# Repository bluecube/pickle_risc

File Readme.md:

# Pickle RISC 16bit CPU

... so I would like to build a computer, this time a little closer to "from scratch".

## Goals
- Fun!
- Aiming for a poorly defined balance between "easy to build" and "not too slow"
- Can run a multitasking OS
- Serve web site about itself (like Magic-1 does)
- Serial console interface
- Run at ~2MHz clock
    - 4MHz as a stretch goal :)
- Most instruction single cycle
- Probably RPi as a peripherial device, emulating a [GPU](notes/graphics.md), network card, storage, serial terminal...

## State
- Instruction set
    - Kind of done, still being tweaked to match the HW limitations and to improve proramming experience
- HW design
    - Slightly more than a fuzzy idea of how stuff should should go together
    - The block diagram shows most of the general idea
    - There is a [design document](design.md) that contains some (incomplete) information
- SW
    - Skeleton of a toolchain written in Rust ([toolchain-rs/](toolchain-rs/))
    - [Lisp](notes/lisp.md) interpreter is planned as a shell
        - Probably loosely based on [Make a Lisp](https://github.com/kanaka/mal/blob/master/process/guide.md)
        - Compiler as a stretch goal

## Links
### Inspiration
- Magic-1: http://www.homebrewcpu.com/
    - Showed me that there is so much magic in this topic.
    - I would like my machine to look like Magic-1 and do the stuff that Magic-1 does.
- Ben Eater's breadboard computer: https://www.youtube.com/playlist?list=PLowKtXNTBypGqImE405J2565dvjafglHU
    - Gave me the idea that I could actually build something like this.
- James Sharman's JAM-1: https://www.youtube.com/c/weirdboyjim/videos
    - Different goals, but just plain awesome :)

### Instruction set
- ARM Thumb Instruction set
- AVR instruction set

### Peripherials
- Interfacing SDHC card to 6502: https://github.com/gfoot/sdcard6502

### The rest
- MUPS/16, a nice 16bit CPU with similar goals/design: http://mups16.net/pages/overview.html#overview
- RISC-V: https://riscv.org/wp-content/uploads/2017/05/riscv-spec-v2.2.pdf
- Simple almost C-like language: https://incoherency.co.uk/blog/stories/slang.html
- Logisim evolution
- Nandgame ALU https://nandgame.com/
    > The ALU (Arithmetic/Logic Unit) performs one or more operations on two input values X and Y.
    >
    > The six flags select what operations to perform. Each flag trigger an operation when the flag is 1:
    > zx	Use 0 for X
    > nx	Invert X
    > zy	Use 0 for Y
    > ny	Invert Y
    > f	selects an operation:
    > 0: output is X AND Y
    > 1: output is X + Y
    > no	Invert output
    >
    > The flags can be combined and the specified order is significant.
    >
    > For example, if both zx and nx is 1, then X is inverted 0.

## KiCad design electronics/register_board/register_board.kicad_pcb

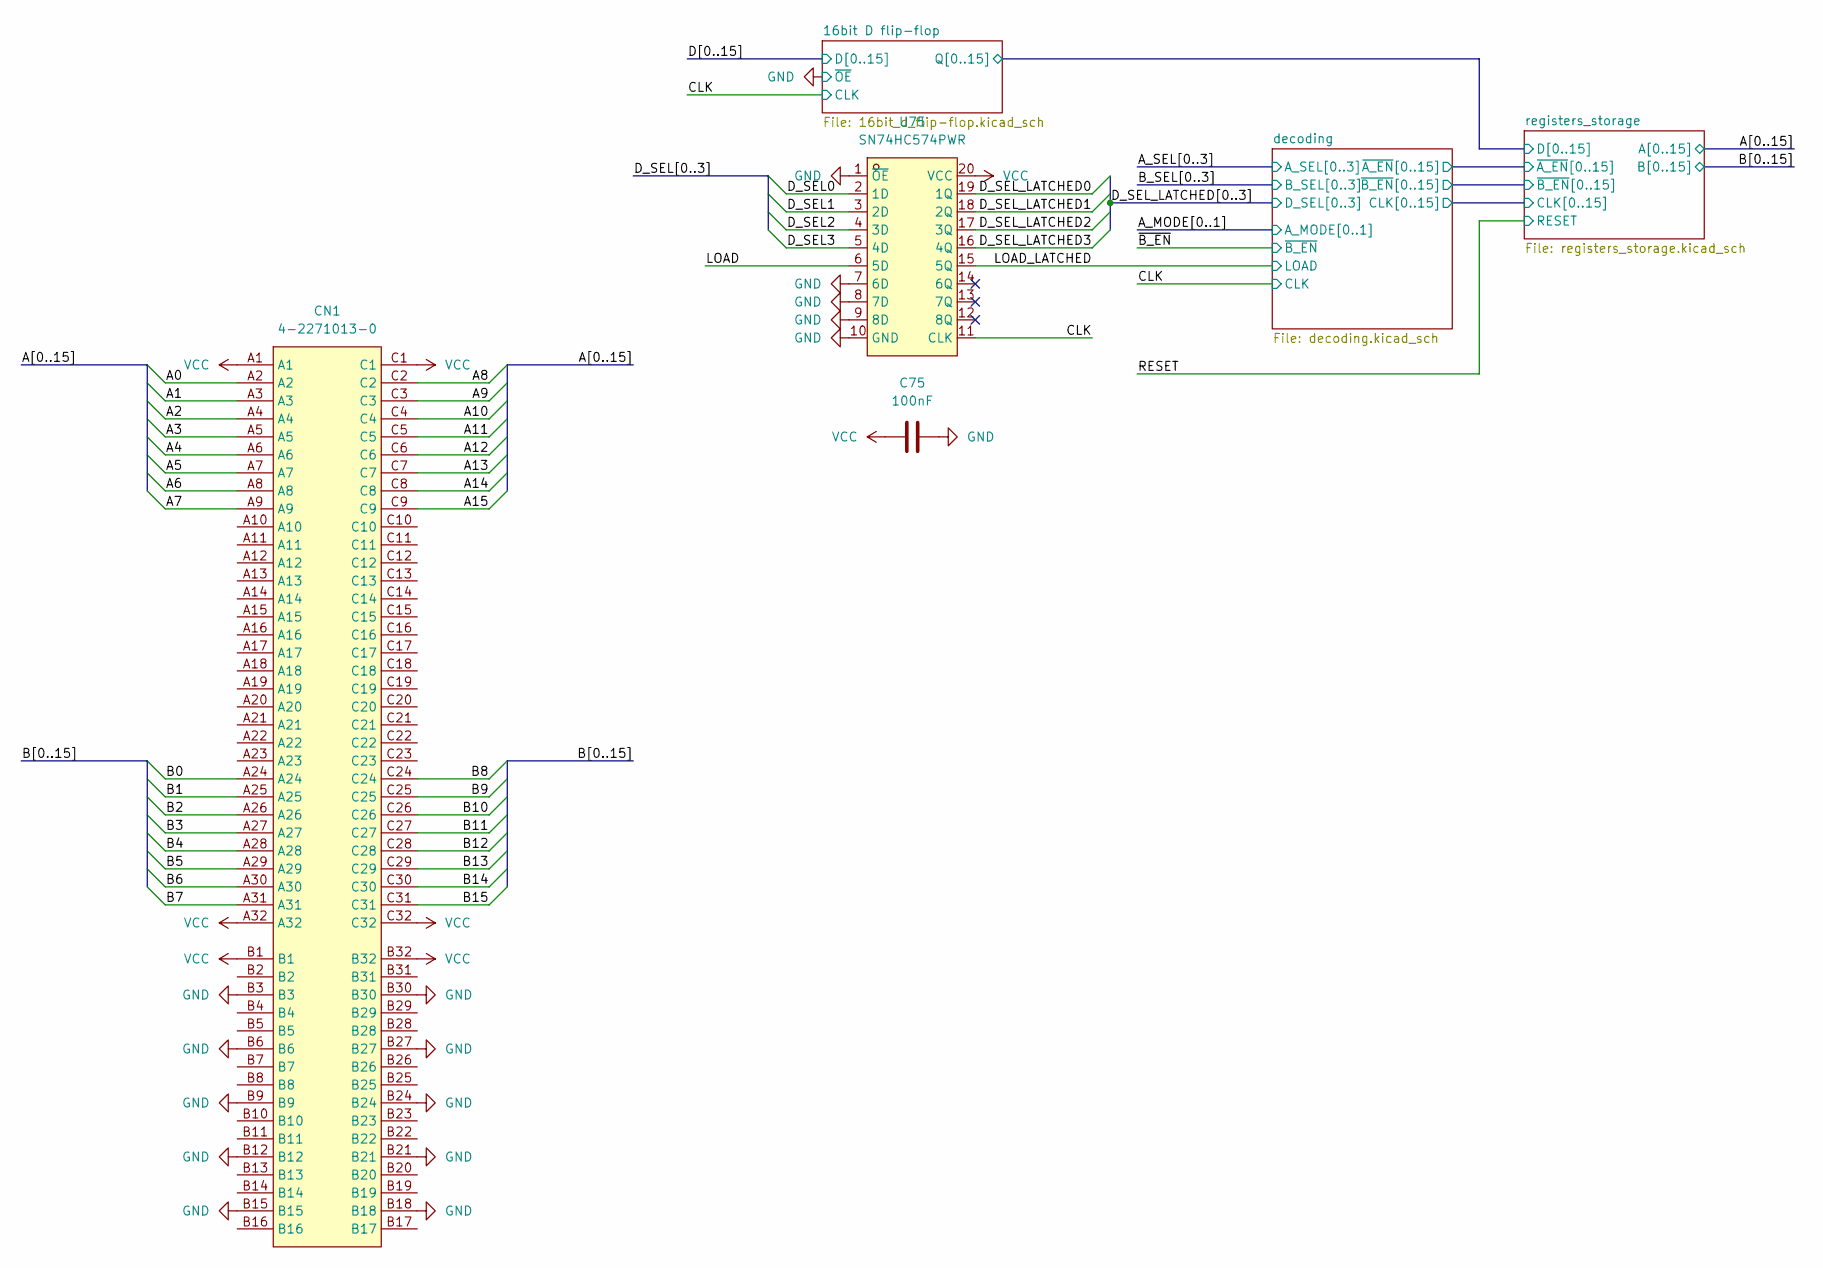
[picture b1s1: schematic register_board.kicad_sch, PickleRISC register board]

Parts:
C75: 100nF; C_0603_1608Metric
CN1: 4-2271013-0; CONN-TH_96P-P2.54_4-2271013-0; LCSC Part C442617
U75: SN74HC574PWR; TSSOP-20_L6.5-W4.4-P0.65-LS6.4-BL; LCSC Part C132111

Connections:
/A0: CN1.A2; also elsewhere on the board
/A1: CN1.A3; also elsewhere on the board
/A2: CN1.A4; also elsewhere on the board
/A3: CN1.A5; also elsewhere on the board
/A4: CN1.A6; also elsewhere on the board
/A5: CN1.A7; also elsewhere on the board
/A6: CN1.A8; also elsewhere on the board
/A7: CN1.A9; also elsewhere on the board
/A8: CN1.C2; also elsewhere on the board
/A9: CN1.C3; also elsewhere on the board
/A10: CN1.C4; also elsewhere on the board
/A11: CN1.C5; also elsewhere on the board
/A12: CN1.C6; also elsewhere on the board
/A13: CN1.C7; also elsewhere on the board
/A14: CN1.C8; also elsewhere on the board
/A15: CN1.C9; also elsewhere on the board
/B0: CN1.A24; also elsewhere on the board
/B1: CN1.A25; also elsewhere on the board
/B2: CN1.A26; also elsewhere on the board
/B3: CN1.A27; also elsewhere on the board
/B4: CN1.A28; also elsewhere on the board
/B5: CN1.A29; also elsewhere on the board
/B6: CN1.A30; also elsewhere on the board
/B7: CN1.A31; also elsewhere on the board
/B8: CN1.C24; also elsewhere on the board
/B9: CN1.C25; also elsewhere on the board
/B10: CN1.C26; also elsewhere on the board
/B11: CN1.C27; also elsewhere on the board
/B12: CN1.C28; also elsewhere on the board
/B13: CN1.C29; also elsewhere on the board
/B14: CN1.C30; also elsewhere on the board
/B15: CN1.C31; also elsewhere on the board
/CLK: U75.11 (CLK); also elsewhere on the board
/D_SEL0: U75.2 (1D)
/D_SEL1: U75.3 (2D)
/D_SEL2: U75.4 (3D)
/D_SEL3: U75.5 (4D)
/D_SEL_LATCHED0: U75.19 (1Q); also elsewhere on the board
/D_SEL_LATCHED1: U75.18 (2Q); also elsewhere on the board
/D_SEL_LATCHED2: U75.17 (3Q); also elsewhere on the board
/D_SEL_LATCHED3: U75.16 (4Q); also elsewhere on the board
/LOAD: U75.6 (5D)
/LOAD_LATCHED: U75.15 (5Q); also elsewhere on the board
GND: C75.2, CN1.B3, CN1.B6, CN1.B9, CN1.B12, CN1.B15, CN1.B18, CN1.B21, CN1.B24, CN1.B27, CN1.B30, U75.1 (~OE), U75.7 (6D), U75.8 (7D), U75.9 (8D), U75.10 (GND); also elsewhere on the board
VCC: C75.1, CN1.A1, CN1.A32, CN1.B1, CN1.B32, CN1.C1, CN1.C32, U75.20 (VCC); also elsewhere on the board

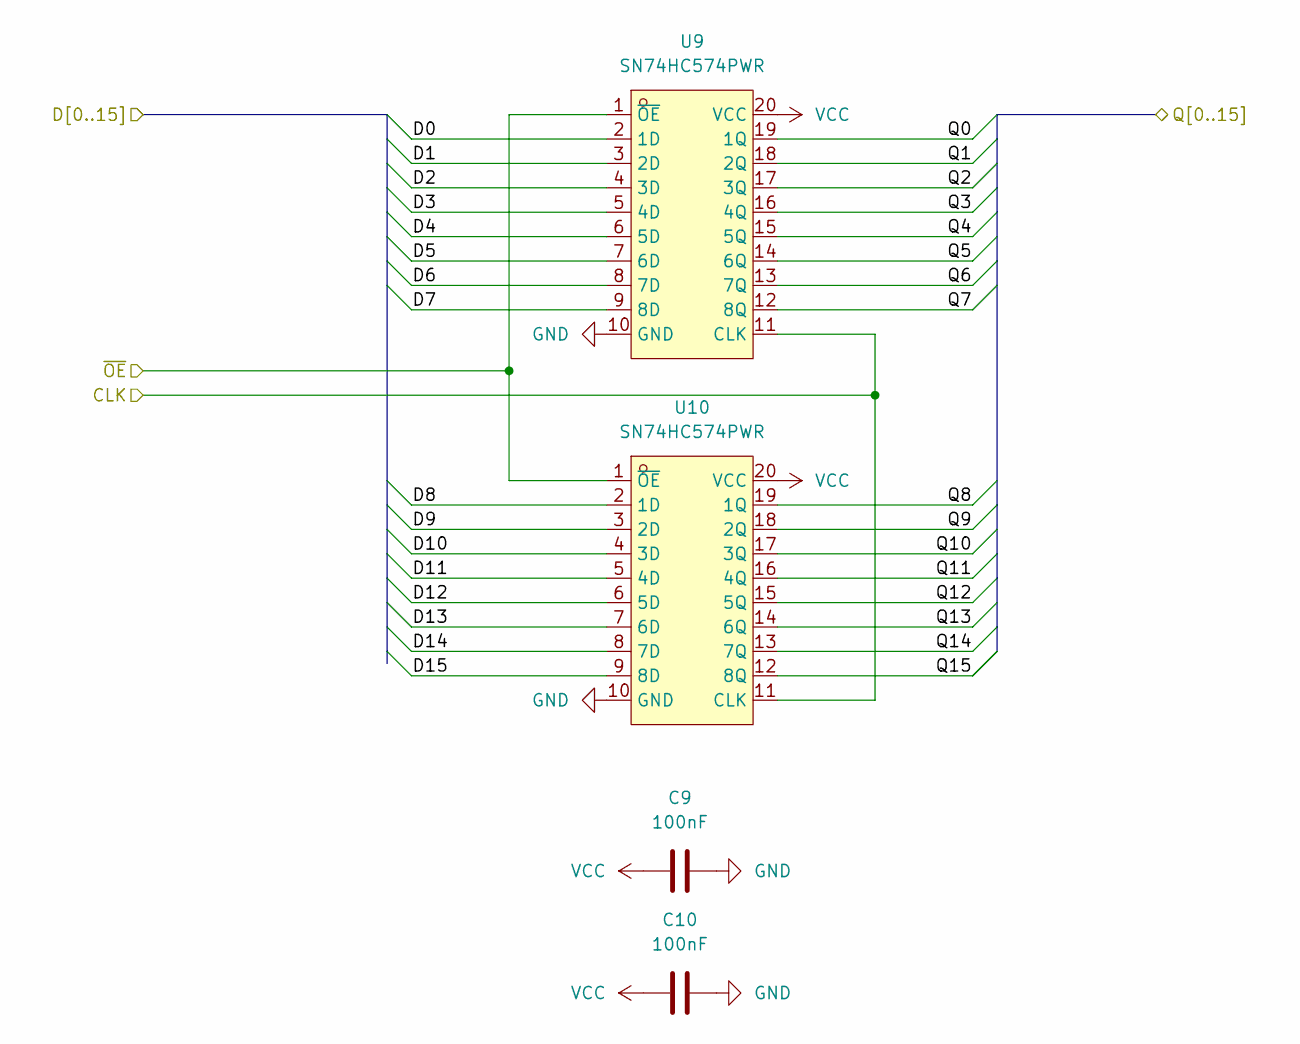
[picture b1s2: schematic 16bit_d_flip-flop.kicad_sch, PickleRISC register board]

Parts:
C9, C10: 100nF; C_0603_1608Metric
U9, U10: SN74HC574PWR; TSSOP-20_L6.5-W4.4-P0.65-LS6.4-BL; LCSC Part C132111

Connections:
/CLK: U9.11 (CLK), U10.11 (CLK); also elsewhere on the board
/D0: U9.2 (1D)
/D1: U9.3 (2D)
/D2: U9.4 (3D)
/D3: U9.5 (4D)
/D4: U9.6 (5D)
/D5: U9.7 (6D)
/D6: U9.8 (7D)
/D7: U9.9 (8D)
/D8: U10.2 (1D)
/D9: U10.3 (2D)
/D10: U10.4 (3D)
/D11: U10.5 (4D)
/D12: U10.6 (5D)
/D13: U10.7 (6D)
/D14: U10.8 (7D)
/D15: U10.9 (8D)
/registers_storage/D0: U9.19 (1Q); also elsewhere on the board
/registers_storage/D1: U9.18 (2Q); also elsewhere on the board
/registers_storage/D2: U9.17 (3Q); also elsewhere on the board
/registers_storage/D3: U9.16 (4Q); also elsewhere on the board
/registers_storage/D4: U9.15 (5Q); also elsewhere on the board
/registers_storage/D5: U9.14 (6Q); also elsewhere on the board
/registers_storage/D6: U9.13 (7Q); also elsewhere on the board
/registers_storage/D7: U9.12 (8Q); also elsewhere on the board
/registers_storage/D8: U10.19 (1Q); also elsewhere on the board
/registers_storage/D9: U10.18 (2Q); also elsewhere on the board
/registers_storage/D10: U10.17 (3Q); also elsewhere on the board
/registers_storage/D11: U10.16 (4Q); also elsewhere on the board
/registers_storage/D12: U10.15 (5Q); also elsewhere on the board
/registers_storage/D13: U10.14 (6Q); also elsewhere on the board
/registers_storage/D14: U10.13 (7Q); also elsewhere on the board
/registers_storage/D15: U10.12 (8Q); also elsewhere on the board
GND: C9.2, C10.2, U9.1 (~OE), U9.10 (GND), U10.1 (~OE), U10.10 (GND); also elsewhere on the board
VCC: C9.1, C10.1, U9.20 (VCC), U10.20 (VCC); also elsewhere on the board

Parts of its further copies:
C15, C16, C17, C18, C19, C20, C21, C22, C23, C24, C25, C26, C27, C28, C29, C30, C31, C32, C33, C34, C35, C36, C37, C38, C39, C40, C41, C42, C43, C44, C45, C46, C47, C48, C49, C50, C51, C52, C53, C54, C55, C56, C57, C58, C59, C60, C61, C62, C63, C64, C65, C66, C67, C68, C69, C70, C71, C72, C73, C74: 100nF; C_0603_1608Metric
U15, U16, U17, U18, U19, U20, U21, U22, U23, U24, U25, U26, U27, U28, U29, U30, U31, U32, U33, U34, U35, U36, U37, U38, U39, U40, U41, U42, U43, U44, U45, U46, U47, U48, U49, U50, U51, U52, U53, U54, U55, U56, U57, U58, U59, U60, U61, U62, U63, U64, U65, U66, U67, U68, U69, U70, U71, U72, U73, U74: SN74HC574PWR; TSSOP-20_L6.5-W4.4-P0.65-LS6.4-BL; LCSC Part C132111

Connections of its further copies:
/A0: U15.19 (1Q), U19.19 (1Q), U23.19 (1Q), U27.19 (1Q), U31.19 (1Q), U35.19 (1Q), U39.19 (1Q), U43.19 (1Q), U47.19 (1Q), U51.19 (1Q), U55.19 (1Q), U59.19 (1Q), U63.19 (1Q), U67.19 (1Q), U71.19 (1Q); also elsewhere on the board
/A1: U15.18 (2Q), U19.18 (2Q), U23.18 (2Q), U27.18 (2Q), U31.18 (2Q), U35.18 (2Q), U39.18 (2Q), U43.18 (2Q), U47.18 (2Q), U51.18 (2Q), U55.18 (2Q), U59.18 (2Q), U63.18 (2Q), U67.18 (2Q), U71.18 (2Q); also elsewhere on the board
/A2: U15.17 (3Q), U19.17 (3Q), U23.17 (3Q), U27.17 (3Q), U31.17 (3Q), U35.17 (3Q), U39.17 (3Q), U43.17 (3Q), U47.17 (3Q), U51.17 (3Q), U55.17 (3Q), U59.17 (3Q), U63.17 (3Q), U67.17 (3Q), U71.17 (3Q); also elsewhere on the board
/A3: U15.16 (4Q), U19.16 (4Q), U23.16 (4Q), U27.16 (4Q), U31.16 (4Q), U35.16 (4Q), U39.16 (4Q), U43.16 (4Q), U47.16 (4Q), U51.16 (4Q), U55.16 (4Q), U59.16 (4Q), U63.16 (4Q), U67.16 (4Q), U71.16 (4Q); also elsewhere on the board
/A4: U15.15 (5Q), U19.15 (5Q), U23.15 (5Q), U27.15 (5Q), U31.15 (5Q), U35.15 (5Q), U39.15 (5Q), U43.15 (5Q), U47.15 (5Q), U51.15 (5Q), U55.15 (5Q), U59.15 (5Q), U63.15 (5Q), U67.15 (5Q), U71.15 (5Q); also elsewhere on the board
/A5: U15.14 (6Q), U19.14 (6Q), U23.14 (6Q), U27.14 (6Q), U31.14 (6Q), U35.14 (6Q), U39.14 (6Q), U43.14 (6Q), U47.14 (6Q), U51.14 (6Q), U55.14 (6Q), U59.14 (6Q), U63.14 (6Q), U67.14 (6Q), U71.14 (6Q); also elsewhere on the board
/A6: U15.13 (7Q), U19.13 (7Q), U23.13 (7Q), U27.13 (7Q), U31.13 (7Q), U35.13 (7Q), U39.13 (7Q), U43.13 (7Q), U47.13 (7Q), U51.13 (7Q), U55.13 (7Q), U59.13 (7Q), U63.13 (7Q), U67.13 (7Q), U71.13 (7Q); also elsewhere on the board
/A7: U15.12 (8Q), U19.12 (8Q), U23.12 (8Q), U27.12 (8Q), U31.12 (8Q), U35.12 (8Q), U39.12 (8Q), U43.12 (8Q), U47.12 (8Q), U51.12 (8Q), U55.12 (8Q), U59.12 (8Q), U63.12 (8Q), U67.12 (8Q), U71.12 (8Q); also elsewhere on the board
/A8: U16.19 (1Q), U20.19 (1Q), U24.19 (1Q), U28.19 (1Q), U32.19 (1Q), U36.19 (1Q), U40.19 (1Q), U44.19 (1Q), U48.19 (1Q), U52.19 (1Q), U56.19 (1Q), U60.19 (1Q), U64.19 (1Q), U68.19 (1Q), U72.19 (1Q); also elsewhere on the board
/A9: U16.18 (2Q), U20.18 (2Q), U24.18 (2Q), U28.18 (2Q), U32.18 (2Q), U36.18 (2Q), U40.18 (2Q), U44.18 (2Q), U48.18 (2Q), U52.18 (2Q), U56.18 (2Q), U60.18 (2Q), U64.18 (2Q), U68.18 (2Q), U72.18 (2Q); also elsewhere on the board
/A10: U16.17 (3Q), U20.17 (3Q), U24.17 (3Q), U28.17 (3Q), U32.17 (3Q), U36.17 (3Q), U40.17 (3Q), U44.17 (3Q), U48.17 (3Q), U52.17 (3Q), U56.17 (3Q), U60.17 (3Q), U64.17 (3Q), U68.17 (3Q), U72.17 (3Q); also elsewhere on the board
/A11: U16.16 (4Q), U20.16 (4Q), U24.16 (4Q), U28.16 (4Q), U32.16 (4Q), U36.16 (4Q), U40.16 (4Q), U44.16 (4Q), U48.16 (4Q), U52.16 (4Q), U56.16 (4Q), U60.16 (4Q), U64.16 (4Q), U68.16 (4Q), U72.16 (4Q); also elsewhere on the board
/A12: U16.15 (5Q), U20.15 (5Q), U24.15 (5Q), U28.15 (5Q), U32.15 (5Q), U36.15 (5Q), U40.15 (5Q), U44.15 (5Q), U48.15 (5Q), U52.15 (5Q), U56.15 (5Q), U60.15 (5Q), U64.15 (5Q), U68.15 (5Q), U72.15 (5Q); also elsewhere on the board
/A13: U16.14 (6Q), U20.14 (6Q), U24.14 (6Q), U28.14 (6Q), U32.14 (6Q), U36.14 (6Q), U40.14 (6Q), U44.14 (6Q), U48.14 (6Q), U52.14 (6Q), U56.14 (6Q), U60.14 (6Q), U64.14 (6Q), U68.14 (6Q), U72.14 (6Q); also elsewhere on the board
/A14: U16.13 (7Q), U20.13 (7Q), U24.13 (7Q), U28.13 (7Q), U32.13 (7Q), U36.13 (7Q), U40.13 (7Q), U44.13 (7Q), U48.13 (7Q), U52.13 (7Q), U56.13 (7Q), U60.13 (7Q), U64.13 (7Q), U68.13 (7Q), U72.13 (7Q); also elsewhere on the board
/A15: U16.12 (8Q), U20.12 (8Q), U24.12 (8Q), U28.12 (8Q), U32.12 (8Q), U36.12 (8Q), U40.12 (8Q), U44.12 (8Q), U48.12 (8Q), U52.12 (8Q), U56.12 (8Q), U60.12 (8Q), U64.12 (8Q), U68.12 (8Q), U72.12 (8Q); also elsewhere on the board
/B0: U17.19 (1Q), U21.19 (1Q), U25.19 (1Q), U29.19 (1Q), U33.19 (1Q), U37.19 (1Q), U41.19 (1Q), U45.19 (1Q), U49.19 (1Q), U53.19 (1Q), U57.19 (1Q), U61.19 (1Q), U65.19 (1Q), U69.19 (1Q), U73.19 (1Q); also elsewhere on the board
/B1: U17.18 (2Q), U21.18 (2Q), U25.18 (2Q), U29.18 (2Q), U33.18 (2Q), U37.18 (2Q), U41.18 (2Q), U45.18 (2Q), U49.18 (2Q), U53.18 (2Q), U57.18 (2Q), U61.18 (2Q), U65.18 (2Q), U69.18 (2Q), U73.18 (2Q); also elsewhere on the board
/B2: U17.17 (3Q), U21.17 (3Q), U25.17 (3Q), U29.17 (3Q), U33.17 (3Q), U37.17 (3Q), U41.17 (3Q), U45.17 (3Q), U49.17 (3Q), U53.17 (3Q), U57.17 (3Q), U61.17 (3Q), U65.17 (3Q), U69.17 (3Q), U73.17 (3Q); also elsewhere on the board
/B3: U17.16 (4Q), U21.16 (4Q), U25.16 (4Q), U29.16 (4Q), U33.16 (4Q), U37.16 (4Q), U41.16 (4Q), U45.16 (4Q), U49.16 (4Q), U53.16 (4Q), U57.16 (4Q), U61.16 (4Q), U65.16 (4Q), U69.16 (4Q), U73.16 (4Q); also elsewhere on the board
/B4: U17.15 (5Q), U21.15 (5Q), U25.15 (5Q), U29.15 (5Q), U33.15 (5Q), U37.15 (5Q), U41.15 (5Q), U45.15 (5Q), U49.15 (5Q), U53.15 (5Q), U57.15 (5Q), U61.15 (5Q), U65.15 (5Q), U69.15 (5Q), U73.15 (5Q); also elsewhere on the board
/B5: U17.14 (6Q), U21.14 (6Q), U25.14 (6Q), U29.14 (6Q), U33.14 (6Q), U37.14 (6Q), U41.14 (6Q), U45.14 (6Q), U49.14 (6Q), U53.14 (6Q), U57.14 (6Q), U61.14 (6Q), U65.14 (6Q), U69.14 (6Q), U73.14 (6Q); also elsewhere on the board
/B6: U17.13 (7Q), U21.13 (7Q), U25.13 (7Q), U29.13 (7Q), U33.13 (7Q), U37.13 (7Q), U41.13 (7Q), U45.13 (7Q), U49.13 (7Q), U53.13 (7Q), U57.13 (7Q), U61.13 (7Q), U65.13 (7Q), U69.13 (7Q), U73.13 (7Q); also elsewhere on the board
/B7: U17.12 (8Q), U21.12 (8Q), U25.12 (8Q), U29.12 (8Q), U33.12 (8Q), U37.12 (8Q), U41.12 (8Q), U45.12 (8Q), U49.12 (8Q), U53.12 (8Q), U57.12 (8Q), U61.12 (8Q), U65.12 (8Q), U69.12 (8Q), U73.12 (8Q); also elsewhere on the board
/B8: U18.19 (1Q), U22.19 (1Q), U26.19 (1Q), U30.19 (1Q), U34.19 (1Q), U38.19 (1Q), U42.19 (1Q), U46.19 (1Q), U50.19 (1Q), U54.19 (1Q), U58.19 (1Q), U62.19 (1Q), U66.19 (1Q), U70.19 (1Q), U74.19 (1Q); also elsewhere on the board
/B9: U18.18 (2Q), U22.18 (2Q), U26.18 (2Q), U30.18 (2Q), U34.18 (2Q), U38.18 (2Q), U42.18 (2Q), U46.18 (2Q), U50.18 (2Q), U54.18 (2Q), U58.18 (2Q), U62.18 (2Q), U66.18 (2Q), U70.18 (2Q), U74.18 (2Q); also elsewhere on the board
/B10: U18.17 (3Q), U22.17 (3Q), U26.17 (3Q), U30.17 (3Q), U34.17 (3Q), U38.17 (3Q), U42.17 (3Q), U46.17 (3Q), U50.17 (3Q), U54.17 (3Q), U58.17 (3Q), U62.17 (3Q), U66.17 (3Q), U70.17 (3Q), U74.17 (3Q); also elsewhere on the board
/B11: U18.16 (4Q), U22.16 (4Q), U26.16 (4Q), U30.16 (4Q), U34.16 (4Q), U38.16 (4Q), U42.16 (4Q), U46.16 (4Q), U50.16 (4Q), U54.16 (4Q), U58.16 (4Q), U62.16 (4Q), U66.16 (4Q), U70.16 (4Q), U74.16 (4Q); also elsewhere on the board
/B12: U18.15 (5Q), U22.15 (5Q), U26.15 (5Q), U30.15 (5Q), U34.15 (5Q), U38.15 (5Q), U42.15 (5Q), U46.15 (5Q), U50.15 (5Q), U54.15 (5Q), U58.15 (5Q), U62.15 (5Q), U66.15 (5Q), U70.15 (5Q), U74.15 (5Q); also elsewhere on the board
/B13: U18.14 (6Q), U22.14 (6Q), U26.14 (6Q), U30.14 (6Q), U34.14 (6Q), U38.14 (6Q), U42.14 (6Q), U46.14 (6Q), U50.14 (6Q), U54.14 (6Q), U58.14 (6Q), U62.14 (6Q), U66.14 (6Q), U70.14 (6Q), U74.14 (6Q); also elsewhere on the board
/B14: U18.13 (7Q), U22.13 (7Q), U26.13 (7Q), U30.13 (7Q), U34.13 (7Q), U38.13 (7Q), U42.13 (7Q), U46.13 (7Q), U50.13 (7Q), U54.13 (7Q), U58.13 (7Q), U62.13 (7Q), U66.13 (7Q), U70.13 (7Q), U74.13 (7Q); also elsewhere on the board
/B15: U18.12 (8Q), U22.12 (8Q), U26.12 (8Q), U30.12 (8Q), U34.12 (8Q), U38.12 (8Q), U42.12 (8Q), U46.12 (8Q), U50.12 (8Q), U54.12 (8Q), U58.12 (8Q), U62.12 (8Q), U66.12 (8Q), U70.12 (8Q), U74.12 (8Q); also elsewhere on the board
/decoding/CLK1: U15.11 (CLK), U16.11 (CLK), U17.11 (CLK), U18.11 (CLK); also elsewhere on the board
/decoding/CLK2: U19.11 (CLK), U20.11 (CLK), U21.11 (CLK), U22.11 (CLK); also elsewhere on the board
/decoding/CLK3: U23.11 (CLK), U24.11 (CLK), U25.11 (CLK), U26.11 (CLK); also elsewhere on the board
/decoding/CLK4: U27.11 (CLK), U28.11 (CLK), U29.11 (CLK), U30.11 (CLK); also elsewhere on the board
/decoding/CLK5: U31.11 (CLK), U32.11 (CLK), U33.11 (CLK), U34.11 (CLK); also elsewhere on the board
/decoding/CLK6: U35.11 (CLK), U36.11 (CLK), U37.11 (CLK), U38.11 (CLK); also elsewhere on the board
/decoding/CLK7: U39.11 (CLK), U40.11 (CLK), U41.11 (CLK), U42.11 (CLK); also elsewhere on the board
/decoding/CLK8: U43.11 (CLK), U44.11 (CLK), U45.11 (CLK), U46.11 (CLK); also elsewhere on the board
/decoding/CLK9: U47.11 (CLK), U48.11 (CLK), U49.11 (CLK), U50.11 (CLK); also elsewhere on the board
/decoding/CLK10: U51.11 (CLK), U52.11 (CLK), U53.11 (CLK), U54.11 (CLK); also elsewhere on the board
/decoding/CLK11: U55.11 (CLK), U56.11 (CLK), U57.11 (CLK), U58.11 (CLK); also elsewhere on the board
/decoding/CLK12: U59.11 (CLK), U60.11 (CLK), U61.11 (CLK), U62.11 (CLK); also elsewhere on the board
/decoding/CLK13: U63.11 (CLK), U64.11 (CLK), U65.11 (CLK), U66.11 (CLK); also elsewhere on the board
/decoding/CLK14: U67.11 (CLK), U68.11 (CLK), U69.11 (CLK), U70.11 (CLK); also elsewhere on the board
/decoding/CLK15: U71.11 (CLK), U72.11 (CLK), U73.11 (CLK), U74.11 (CLK); also elsewhere on the board
/decoding/~A_EN1: U15.1 (~OE), U16.1 (~OE); also elsewhere on the board
/decoding/~A_EN2: U19.1 (~OE), U20.1 (~OE); also elsewhere on the board
/decoding/~A_EN3: U23.1 (~OE), U24.1 (~OE); also elsewhere on the board
/decoding/~A_EN4: U27.1 (~OE), U28.1 (~OE); also elsewhere on the board
/decoding/~A_EN5: U31.1 (~OE), U32.1 (~OE); also elsewhere on the board
/decoding/~A_EN6: U35.1 (~OE), U36.1 (~OE); also elsewhere on the board
/decoding/~A_EN7: U39.1 (~OE), U40.1 (~OE); also elsewhere on the board
/decoding/~A_EN8: U43.1 (~OE), U44.1 (~OE); also elsewhere on the board
/decoding/~A_EN9: U47.1 (~OE), U48.1 (~OE); also elsewhere on the board
/decoding/~A_EN10: U51.1 (~OE), U52.1 (~OE); also elsewhere on the board
/decoding/~A_EN11: U55.1 (~OE), U56.1 (~OE); also elsewhere on the board
/decoding/~A_EN12: U59.1 (~OE), U60.1 (~OE); also elsewhere on the board
/decoding/~A_EN13: U63.1 (~OE), U64.1 (~OE); also elsewhere on the board
/decoding/~A_EN14: U67.1 (~OE), U68.1 (~OE); also elsewhere on the board
/decoding/~A_EN15: U71.1 (~OE), U72.1 (~OE); also elsewhere on the board
/decoding/~B_EN1: U17.1 (~OE), U18.1 (~OE); also elsewhere on the board
/decoding/~B_EN2: U21.1 (~OE), U22.1 (~OE); also elsewhere on the board
/decoding/~B_EN3: U25.1 (~OE), U26.1 (~OE); also elsewhere on the board
/decoding/~B_EN4: U29.1 (~OE), U30.1 (~OE); also elsewhere on the board
/decoding/~B_EN5: U33.1 (~OE), U34.1 (~OE); also elsewhere on the board
/decoding/~B_EN6: U37.1 (~OE), U38.1 (~OE); also elsewhere on the board
/decoding/~B_EN7: U41.1 (~OE), U42.1 (~OE); also elsewhere on the board
/decoding/~B_EN8: U45.1 (~OE), U46.1 (~OE); also elsewhere on the board
/decoding/~B_EN9: U49.1 (~OE), U50.1 (~OE); also elsewhere on the board
/decoding/~B_EN10: U53.1 (~OE), U54.1 (~OE); also elsewhere on the board
/decoding/~B_EN11: U57.1 (~OE), U58.1 (~OE); also elsewhere on the board
/decoding/~B_EN12: U61.1 (~OE), U62.1 (~OE); also elsewhere on the board
/decoding/~B_EN13: U65.1 (~OE), U66.1 (~OE); also elsewhere on the board
/decoding/~B_EN14: U69.1 (~OE), U70.1 (~OE); also elsewhere on the board
/decoding/~B_EN15: U73.1 (~OE), U74.1 (~OE); also elsewhere on the board
/registers_storage/D0: U15.2 (1D), U17.2 (1D), U19.2 (1D), U21.2 (1D), U23.2 (1D), U25.2 (1D), U27.2 (1D), U29.2 (1D), U31.2 (1D), U33.2 (1D), U35.2 (1D), U37.2 (1D), U39.2 (1D), U41.2 (1D), U43.2 (1D), U45.2 (1D), U47.2 (1D), U49.2 (1D), U51.2 (1D), U53.2 (1D), U55.2 (1D), U57.2 (1D), U59.2 (1D), U61.2 (1D), U63.2 (1D), U65.2 (1D), U67.2 (1D), U69.2 (1D), U71.2 (1D), U73.2 (1D); also elsewhere on the board
/registers_storage/D1: U15.3 (2D), U17.3 (2D), U19.3 (2D), U21.3 (2D), U23.3 (2D), U25.3 (2D), U27.3 (2D), U29.3 (2D), U31.3 (2D), U33.3 (2D), U35.3 (2D), U37.3 (2D), U39.3 (2D), U41.3 (2D), U43.3 (2D), U45.3 (2D), U47.3 (2D), U49.3 (2D), U51.3 (2D), U53.3 (2D), U55.3 (2D), U57.3 (2D), U59.3 (2D), U61.3 (2D), U63.3 (2D), U65.3 (2D), U67.3 (2D), U69.3 (2D), U71.3 (2D), U73.3 (2D); also elsewhere on the board
/registers_storage/D2: U15.4 (3D), U17.4 (3D), U19.4 (3D), U21.4 (3D), U23.4 (3D), U25.4 (3D), U27.4 (3D), U29.4 (3D), U31.4 (3D), U33.4 (3D), U35.4 (3D), U37.4 (3D), U39.4 (3D), U41.4 (3D), U43.4 (3D), U45.4 (3D), U47.4 (3D), U49.4 (3D), U51.4 (3D), U53.4 (3D), U55.4 (3D), U57.4 (3D), U59.4 (3D), U61.4 (3D), U63.4 (3D), U65.4 (3D), U67.4 (3D), U69.4 (3D), U71.4 (3D), U73.4 (3D); also elsewhere on the board
/registers_storage/D3: U15.5 (4D), U17.5 (4D), U19.5 (4D), U21.5 (4D), U23.5 (4D), U25.5 (4D), U27.5 (4D), U29.5 (4D), U31.5 (4D), U33.5 (4D), U35.5 (4D), U37.5 (4D), U39.5 (4D), U41.5 (4D), U43.5 (4D), U45.5 (4D), U47.5 (4D), U49.5 (4D), U51.5 (4D), U53.5 (4D), U55.5 (4D), U57.5 (4D), U59.5 (4D), U61.5 (4D), U63.5 (4D), U65.5 (4D), U67.5 (4D), U69.5 (4D), U71.5 (4D), U73.5 (4D); also elsewhere on the board
/registers_storage/D4: U15.6 (5D), U17.6 (5D), U19.6 (5D), U21.6 (5D), U23.6 (5D), U25.6 (5D), U27.6 (5D), U29.6 (5D), U31.6 (5D), U33.6 (5D), U35.6 (5D), U37.6 (5D), U39.6 (5D), U41.6 (5D), U43.6 (5D), U45.6 (5D), U47.6 (5D), U49.6 (5D), U51.6 (5D), U53.6 (5D), U55.6 (5D), U57.6 (5D), U59.6 (5D), U61.6 (5D), U63.6 (5D), U65.6 (5D), U67.6 (5D), U69.6 (5D), U71.6 (5D), U73.6 (5D); also elsewhere on the board
/registers_storage/D5: U15.7 (6D), U17.7 (6D), U19.7 (6D), U21.7 (6D), U23.7 (6D), U25.7 (6D), U27.7 (6D), U29.7 (6D), U31.7 (6D), U33.7 (6D), U35.7 (6D), U37.7 (6D), U39.7 (6D), U41.7 (6D), U43.7 (6D), U45.7 (6D), U47.7 (6D), U49.7 (6D), U51.7 (6D), U53.7 (6D), U55.7 (6D), U57.7 (6D), U59.7 (6D), U61.7 (6D), U63.7 (6D), U65.7 (6D), U67.7 (6D), U69.7 (6D), U71.7 (6D), U73.7 (6D); also elsewhere on the board
/registers_storage/D6: U15.8 (7D), U17.8 (7D), U19.8 (7D), U21.8 (7D), U23.8 (7D), U25.8 (7D), U27.8 (7D), U29.8 (7D), U31.8 (7D), U33.8 (7D), U35.8 (7D), U37.8 (7D), U39.8 (7D), U41.8 (7D), U43.8 (7D), U45.8 (7D), U47.8 (7D), U49.8 (7D), U51.8 (7D), U53.8 (7D), U55.8 (7D), U57.8 (7D), U59.8 (7D), U61.8 (7D), U63.8 (7D), U65.8 (7D), U67.8 (7D), U69.8 (7D), U71.8 (7D), U73.8 (7D); also elsewhere on the board
/registers_storage/D7: U15.9 (8D), U17.9 (8D), U19.9 (8D), U21.9 (8D), U23.9 (8D), U25.9 (8D), U27.9 (8D), U29.9 (8D), U31.9 (8D), U33.9 (8D), U35.9 (8D), U37.9 (8D), U39.9 (8D), U41.9 (8D), U43.9 (8D), U45.9 (8D), U47.9 (8D), U49.9 (8D), U51.9 (8D), U53.9 (8D), U55.9 (8D), U57.9 (8D), U59.9 (8D), U61.9 (8D), U63.9 (8D), U65.9 (8D), U67.9 (8D), U69.9 (8D), U71.9 (8D), U73.9 (8D); also elsewhere on the board
/registers_storage/D8: U16.2 (1D), U18.2 (1D), U20.2 (1D), U22.2 (1D), U24.2 (1D), U26.2 (1D), U28.2 (1D), U30.2 (1D), U32.2 (1D), U34.2 (1D), U36.2 (1D), U38.2 (1D), U40.2 (1D), U42.2 (1D), U44.2 (1D), U46.2 (1D), U48.2 (1D), U50.2 (1D), U52.2 (1D), U54.2 (1D), U56.2 (1D), U58.2 (1D), U60.2 (1D), U62.2 (1D), U64.2 (1D), U66.2 (1D), U68.2 (1D), U70.2 (1D), U72.2 (1D), U74.2 (1D); also elsewhere on the board
/registers_storage/D9: U16.3 (2D), U18.3 (2D), U20.3 (2D), U22.3 (2D), U24.3 (2D), U26.3 (2D), U28.3 (2D), U30.3 (2D), U32.3 (2D), U34.3 (2D), U36.3 (2D), U38.3 (2D), U40.3 (2D), U42.3 (2D), U44.3 (2D), U46.3 (2D), U48.3 (2D), U50.3 (2D), U52.3 (2D), U54.3 (2D), U56.3 (2D), U58.3 (2D), U60.3 (2D), U62.3 (2D), U64.3 (2D), U66.3 (2D), U68.3 (2D), U70.3 (2D), U72.3 (2D), U74.3 (2D); also elsewhere on the board
/registers_storage/D10: U16.4 (3D), U18.4 (3D), U20.4 (3D), U22.4 (3D), U24.4 (3D), U26.4 (3D), U28.4 (3D), U30.4 (3D), U32.4 (3D), U34.4 (3D), U36.4 (3D), U38.4 (3D), U40.4 (3D), U42.4 (3D), U44.4 (3D), U46.4 (3D), U48.4 (3D), U50.4 (3D), U52.4 (3D), U54.4 (3D), U56.4 (3D), U58.4 (3D), U60.4 (3D), U62.4 (3D), U64.4 (3D), U66.4 (3D), U68.4 (3D), U70.4 (3D), U72.4 (3D), U74.4 (3D); also elsewhere on the board
/registers_storage/D11: U16.5 (4D), U18.5 (4D), U20.5 (4D), U22.5 (4D), U24.5 (4D), U26.5 (4D), U28.5 (4D), U30.5 (4D), U32.5 (4D), U34.5 (4D), U36.5 (4D), U38.5 (4D), U40.5 (4D), U42.5 (4D), U44.5 (4D), U46.5 (4D), U48.5 (4D), U50.5 (4D), U52.5 (4D), U54.5 (4D), U56.5 (4D), U58.5 (4D), U60.5 (4D), U62.5 (4D), U64.5 (4D), U66.5 (4D), U68.5 (4D), U70.5 (4D), U72.5 (4D), U74.5 (4D); also elsewhere on the board
/registers_storage/D12: U16.6 (5D), U18.6 (5D), U20.6 (5D), U22.6 (5D), U24.6 (5D), U26.6 (5D), U28.6 (5D), U30.6 (5D), U32.6 (5D), U34.6 (5D), U36.6 (5D), U38.6 (5D), U40.6 (5D), U42.6 (5D), U44.6 (5D), U46.6 (5D), U48.6 (5D), U50.6 (5D), U52.6 (5D), U54.6 (5D), U56.6 (5D), U58.6 (5D), U60.6 (5D), U62.6 (5D), U64.6 (5D), U66.6 (5D), U68.6 (5D), U70.6 (5D), U72.6 (5D), U74.6 (5D); also elsewhere on the board
/registers_storage/D13: U16.7 (6D), U18.7 (6D), U20.7 (6D), U22.7 (6D), U24.7 (6D), U26.7 (6D), U28.7 (6D), U30.7 (6D), U32.7 (6D), U34.7 (6D), U36.7 (6D), U38.7 (6D), U40.7 (6D), U42.7 (6D), U44.7 (6D), U46.7 (6D), U48.7 (6D), U50.7 (6D), U52.7 (6D), U54.7 (6D), U56.7 (6D), U58.7 (6D), U60.7 (6D), U62.7 (6D), U64.7 (6D), U66.7 (6D), U68.7 (6D), U70.7 (6D), U72.7 (6D), U74.7 (6D); also elsewhere on the board
/registers_storage/D14: U16.8 (7D), U18.8 (7D), U20.8 (7D), U22.8 (7D), U24.8 (7D), U26.8 (7D), U28.8 (7D), U30.8 (7D), U32.8 (7D), U34.8 (7D), U36.8 (7D), U38.8 (7D), U40.8 (7D), U42.8 (7D), U44.8 (7D), U46.8 (7D), U48.8 (7D), U50.8 (7D), U52.8 (7D), U54.8 (7D), U56.8 (7D), U58.8 (7D), U60.8 (7D), U62.8 (7D), U64.8 (7D), U66.8 (7D), U68.8 (7D), U70.8 (7D), U72.8 (7D), U74.8 (7D); also elsewhere on the board
/registers_storage/D15: U16.9 (8D), U18.9 (8D), U20.9 (8D), U22.9 (8D), U24.9 (8D), U26.9 (8D), U28.9 (8D), U30.9 (8D), U32.9 (8D), U34.9 (8D), U36.9 (8D), U38.9 (8D), U40.9 (8D), U42.9 (8D), U44.9 (8D), U46.9 (8D), U48.9 (8D), U50.9 (8D), U52.9 (8D), U54.9 (8D), U56.9 (8D), U58.9 (8D), U60.9 (8D), U62.9 (8D), U64.9 (8D), U66.9 (8D), U68.9 (8D), U70.9 (8D), U72.9 (8D), U74.9 (8D); also elsewhere on the board
GND: C15.2, C16.2, C17.2, C18.2, C19.2, C20.2, C21.2, C22.2, C23.2, C24.2, C25.2, C26.2, C27.2, C28.2, C29.2, C30.2, C31.2, C32.2, C33.2, C34.2, C35.2, C36.2, C37.2, C38.2, C39.2, C40.2, C41.2, C42.2, C43.2, C44.2, C45.2, C46.2, C47.2, C48.2, C49.2, C50.2, C51.2, C52.2, C53.2, C54.2, C55.2, C56.2, C57.2, C58.2, C59.2, C60.2, C61.2, C62.2, C63.2, C64.2, C65.2, C66.2, C67.2, C68.2, C69.2, C70.2, C71.2, C72.2, C73.2, C74.2, U15.10 (GND), U16.10 (GND), U17.10 (GND), U18.10 (GND), U19.10 (GND), U20.10 (GND), U21.10 (GND), U22.10 (GND), U23.10 (GND), U24.10 (GND), U25.10 (GND), U26.10 (GND), U27.10 (GND), U28.10 (GND), U29.10 (GND), U30.10 (GND), U31.10 (GND), U32.10 (GND), U33.10 (GND), U34.10 (GND), U35.10 (GND), U36.10 (GND), U37.10 (GND), U38.10 (GND), U39.10 (GND), U40.10 (GND), U41.10 (GND), U42.10 (GND), U43.10 (GND), U44.10 (GND), U45.10 (GND), U46.10 (GND), U47.10 (GND), U48.10 (GND), U49.10 (GND), U50.10 (GND), U51.10 (GND), U52.10 (GND), U53.10 (GND), U54.10 (GND), U55.10 (GND), U56.10 (GND), U57.10 (GND), U58.10 (GND), U59.10 (GND), U60.10 (GND), U61.10 (GND), U62.10 (GND), U63.10 (GND), U64.10 (GND), U65.10 (GND), U66.10 (GND), U67.10 (GND), U68.10 (GND), U69.10 (GND), U70.10 (GND), U71.10 (GND), U72.10 (GND), U73.10 (GND), U74.10 (GND); also elsewhere on the board
VCC: C15.1, C16.1, C17.1, C18.1, C19.1, C20.1, C21.1, C22.1, C23.1, C24.1, C25.1, C26.1, C27.1, C28.1, C29.1, C30.1, C31.1, C32.1, C33.1, C34.1, C35.1, C36.1, C37.1, C38.1, C39.1, C40.1, C41.1, C42.1, C43.1, C44.1, C45.1, C46.1, C47.1, C48.1, C49.1, C50.1, C51.1, C52.1, C53.1, C54.1, C55.1, C56.1, C57.1, C58.1, C59.1, C60.1, C61.1, C62.1, C63.1, C64.1, C65.1, C66.1, C67.1, C68.1, C69.1, C70.1, C71.1, C72.1, C73.1, C74.1, U15.20 (VCC), U16.20 (VCC), U17.20 (VCC), U18.20 (VCC), U19.20 (VCC), U20.20 (VCC), U21.20 (VCC), U22.20 (VCC), U23.20 (VCC), U24.20 (VCC), U25.20 (VCC), U26.20 (VCC), U27.20 (VCC), U28.20 (VCC), U29.20 (VCC), U30.20 (VCC), U31.20 (VCC), U32.20 (VCC), U33.20 (VCC), U34.20 (VCC), U35.20 (VCC), U36.20 (VCC), U37.20 (VCC), U38.20 (VCC), U39.20 (VCC), U40.20 (VCC), U41.20 (VCC), U42.20 (VCC), U43.20 (VCC), U44.20 (VCC), U45.20 (VCC), U46.20 (VCC), U47.20 (VCC), U48.20 (VCC), U49.20 (VCC), U50.20 (VCC), U51.20 (VCC), U52.20 (VCC), U53.20 (VCC), U54.20 (VCC), U55.20 (VCC), U56.20 (VCC), U57.20 (VCC), U58.20 (VCC), U59.20 (VCC), U60.20 (VCC), U61.20 (VCC), U62.20 (VCC), U63.20 (VCC), U64.20 (VCC), U65.20 (VCC), U66.20 (VCC), U67.20 (VCC), U68.20 (VCC), U69.20 (VCC), U70.20 (VCC), U71.20 (VCC), U72.20 (VCC), U73.20 (VCC), U74.20 (VCC); also elsewhere on the board

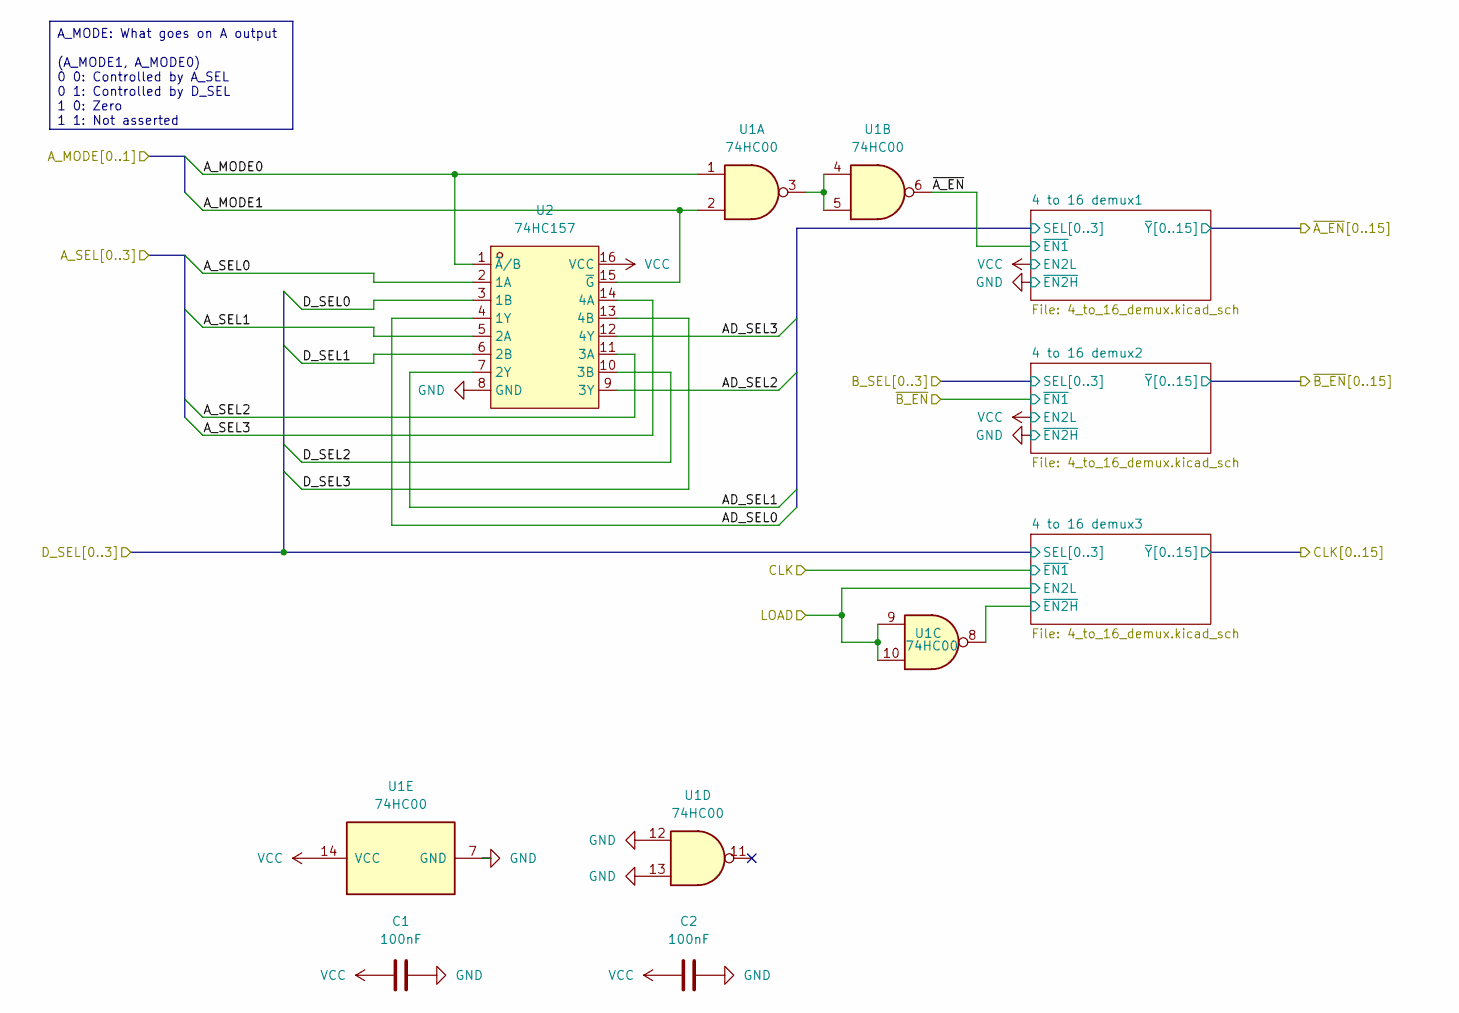
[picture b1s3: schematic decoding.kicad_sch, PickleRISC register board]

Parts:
C1, C2: 100nF; C_0603_1608Metric
U1: 74HC00; TSSOP-14_L5.0-W4.4-P0.65-LS6.4-BL
U2: 74HC157; TSSOP-16_L5.0-W4.4-P0.65-LS6.4-BL; LCSC Part C408973

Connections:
/A_MODE0: U1.1, U2.1 (~A/B)
/A_MODE1: U1.2, U2.15 (~G)
/A_SEL0: U2.2 (1A)
/A_SEL1: U2.5 (2A)
/A_SEL2: U2.11 (3A)
/A_SEL3: U2.14 (4A)
/D_SEL_LATCHED0: U2.3 (1B); also elsewhere on the board
/D_SEL_LATCHED1: U2.6 (2B); also elsewhere on the board
/D_SEL_LATCHED2: U2.10 (3B); also elsewhere on the board
/D_SEL_LATCHED3: U2.13 (4B); also elsewhere on the board
/LOAD_LATCHED: U1.9, U1.10; also elsewhere on the board
/decoding/4 to 16 demux3/~EN2H: U1.8; also elsewhere on the board
/decoding/AD_SEL0: U2.4 (1Y)
/decoding/AD_SEL1: U2.7 (2Y)
/decoding/AD_SEL2: U2.9 (3Y)
/decoding/AD_SEL3: U2.12 (4Y)
/decoding/~A_EN: U1.6; also elsewhere on the board
GND: C1.2, C2.2, U1.7 (GND), U1.12, U1.13, U2.8 (GND); also elsewhere on the board
unnamed: U1.3, U1.4, U1.5
VCC: C1.1, C2.1, U1.14 (VCC), U2.16 (VCC); also elsewhere on the board

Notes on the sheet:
A_MODE: What goes on A output (A_MODE1, A_MODE0) 0 0: Controlled by A_SEL 0 1: Controlled by D_SEL 1 0: Zero 1 1: Not asserted
